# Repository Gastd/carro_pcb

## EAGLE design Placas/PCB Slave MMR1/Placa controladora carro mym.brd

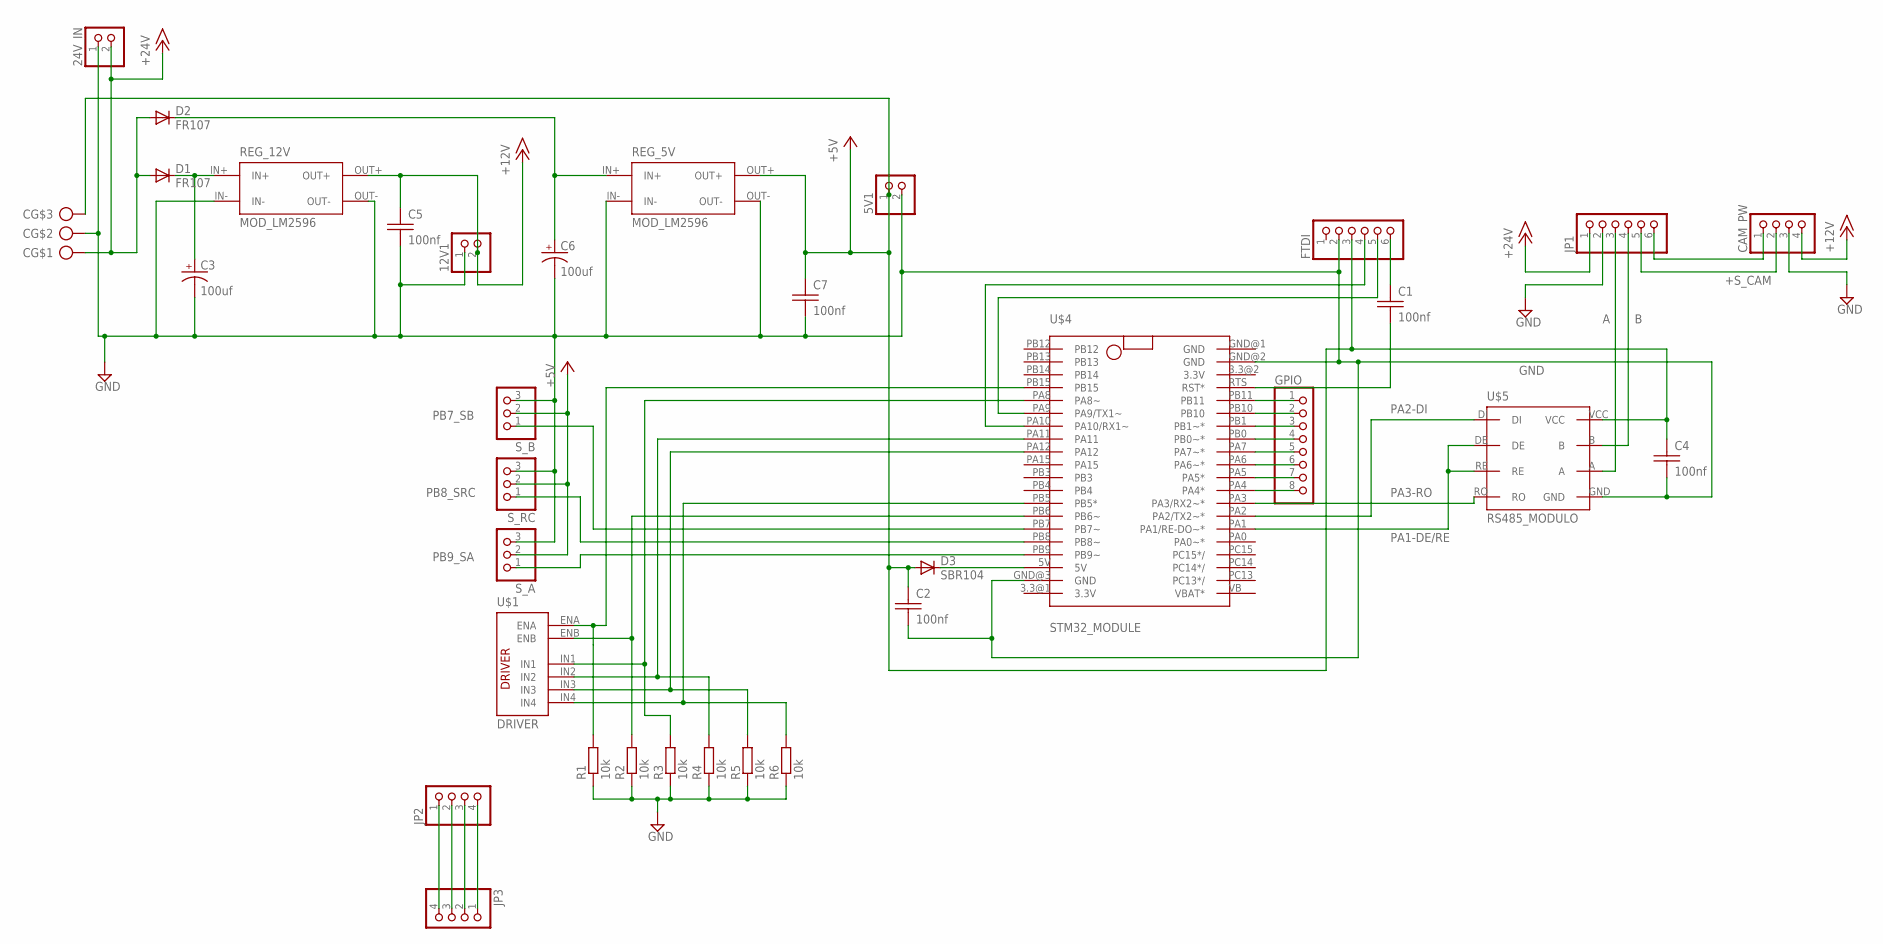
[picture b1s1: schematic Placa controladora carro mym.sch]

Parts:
5V1, 12V1, 24V_IN: PINHD-1X2; 1X02
C: drv; PTR_AK300/3
C1, C2, C4, C5, C7: 100nf; CAP_CER_2,54-5X5
C3, C6: 100uf; CAP_T_5-D8,5
CAM_PW: PINHD-1X4; 1X04
D1, D2: FR107; D-2.5
D3: SBR104; D_SMD
FTDI: PINHD-1X6; 1X06
GPIO: PINHD-1X8; 1X08
JP1: PINHD-1X6; 1X06
JP2, JP3: PINHD-1X4; 1X04
R1, R2, R3, R4, R5, R6: 10k; 0204/7
REG_5V, REG_12V: MOD_LM2596; MOD_LM2596_FP
S_A: PINHD-1X3; 1X03
S_B: PINHD-1X3; 1X03
S_RC: PINHD-1X3; 1X03
U$1: DRIVER
U$4: STM32_MODULE; STM32FP
U$5: RS485_MODULO; RS485_FP

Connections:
+5V: 5V1.1, C.3, C2.1, C4.1, C7.1, D3.A, FTDI.3, REG_5V.OUT+, S_A.2, S_B.2, S_RC.2, U$5.VCC
+12V: 12V1.2, C5.1, REG_12V.OUT+
+15V: 24V_IN.2, C.1, CAM_PW.4, D1.A, D2.A, JP1.1
+S_CAM: CAM_PW.2, JP1.5
A: JP1.3, U$5.A
B: JP1.4, U$5.B
ENA: R1.2, U$1.ENA, U$4.PB15
ENEB: R2.2, U$1.ENB, U$4.PB6 (PB6~)
GND: 5V1.2, 12V1.1, 24V_IN.1, C.2, C2.2, C3.-, C4.2, C5.2, C6.-, C7.2, CAM_PW.3, FTDI.2, JP1.2, R1.1, R2.1, R3.1, R4.1, R5.1, R6.1, REG_5V.IN-, REG_5V.OUT-, REG_12V.IN-, REG_12V.OUT-, S_A.3, S_B.3, S_RC.3, U$4.GND@2 (GND), U$4.GND@3 (GND), U$5.GND
IN1: R3.2, U$1.IN1, U$4.PA8 (PA8~)
IN2: R4.2, U$1.IN2, U$4.PA11
IN3: R5.2, U$1.IN3, U$4.PA12
IN4: R6.2, U$1.IN4, U$4.PB5 (PB5*)
unnamed: D3.K (C), U$4.5V
unnamed: C6.+, D2.C, REG_5V.IN+
unnamed: C3.+, D1.C, REG_12V.IN+
unnamed: CAM_PW.1, JP1.6
unnamed: JP2.1, JP3.4
unnamed: FTDI.4, U$4.PA10 (PA10/RX1~)
unnamed: FTDI.5, U$4.PA9 (PA9/TX1~)
unnamed: C1.1, FTDI.6
unnamed: C1.2, U$4.RTS (RST*)
unnamed: JP2.2, JP3.3
unnamed: JP2.3, JP3.2
unnamed: JP2.4, JP3.1
unnamed: GPIO.1, U$4.PB11
unnamed: GPIO.2, U$4.PB10
unnamed: GPIO.3, U$4.PB1 (PB1~*)
unnamed: GPIO.4, U$4.PB0 (PB0~*)
unnamed: GPIO.5, U$4.PA7 (PA7~*)
unnamed: GPIO.6, U$4.PA6 (PA6~*)
unnamed: GPIO.7, U$4.PA5 (PA5*)
unnamed: GPIO.8, U$4.PA4 (PA4*)
PA1-DE/RE: U$4.PA1 (PA1/RE-DO~*), U$5.DE, U$5.RE
PA2-DI: U$4.PA2 (PA2/TX2~*), U$5.DI
PA3-RO: U$4.PA3 (PA3/RX2~*), U$5.RO
PB7_SB: S_B.1, U$4.PB7 (PB7~)
PB8_SRC: S_RC.1, U$4.PB8 (PB8~)
PB9_SA: S_A.1, U$4.PB9 (PB9~)

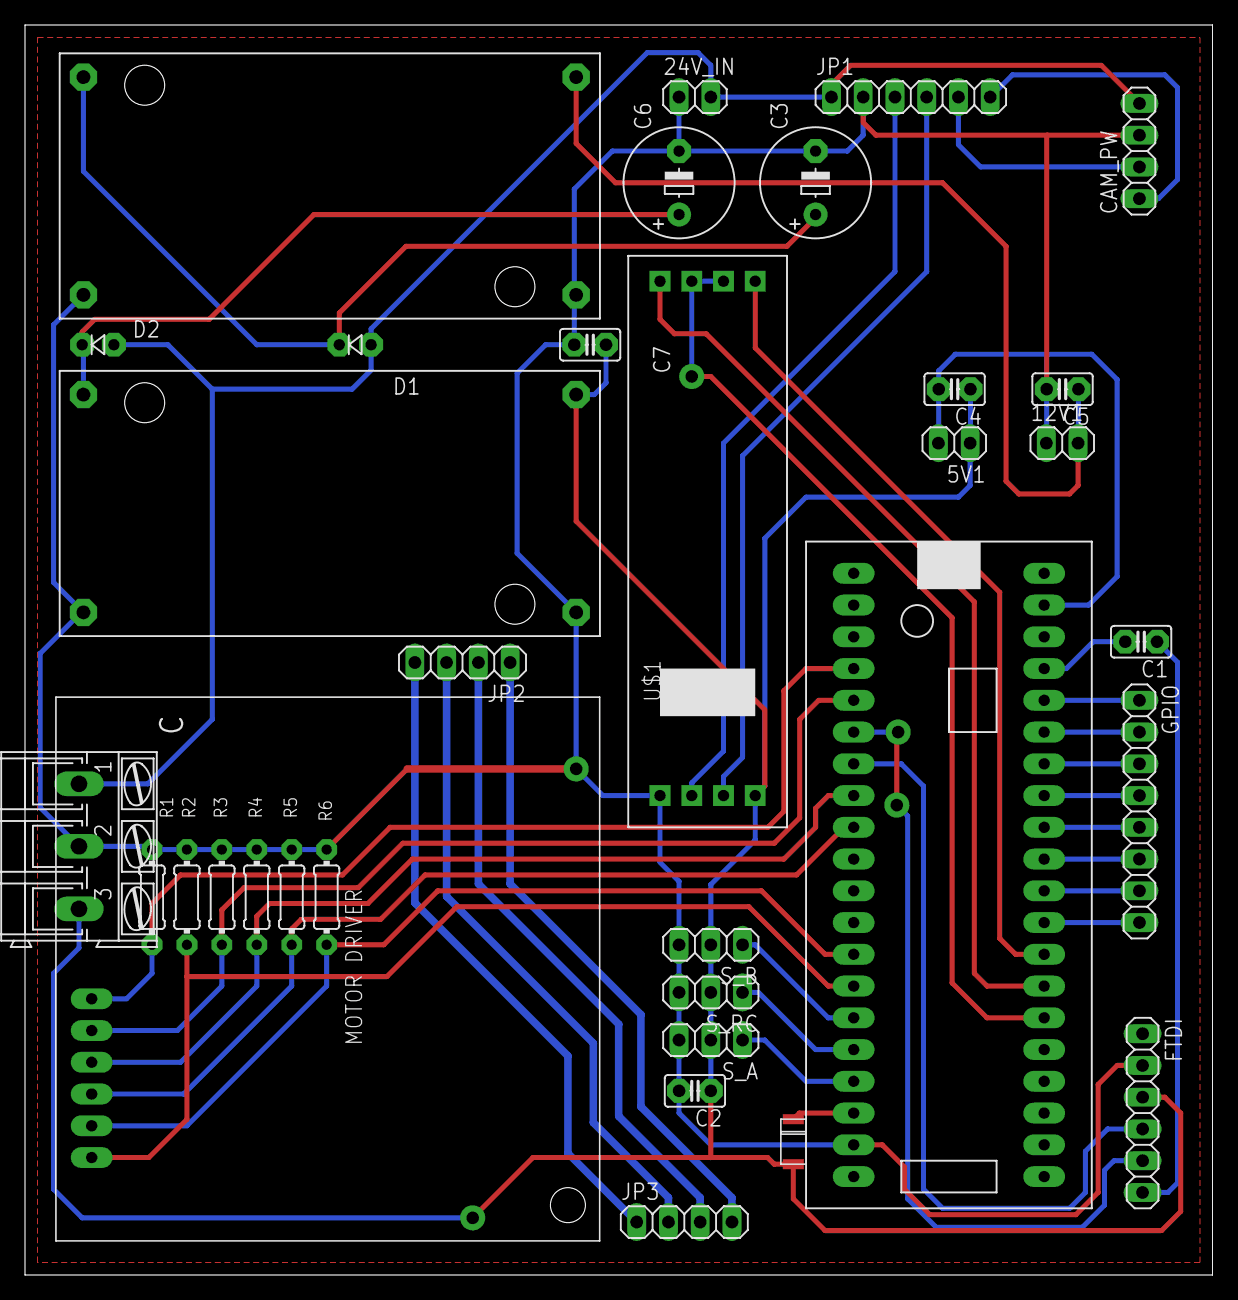
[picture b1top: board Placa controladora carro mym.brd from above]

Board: 2 copper layers, 95.0 x 100.0 mm, 34 parts (0 on the bottom side), 39 nets.

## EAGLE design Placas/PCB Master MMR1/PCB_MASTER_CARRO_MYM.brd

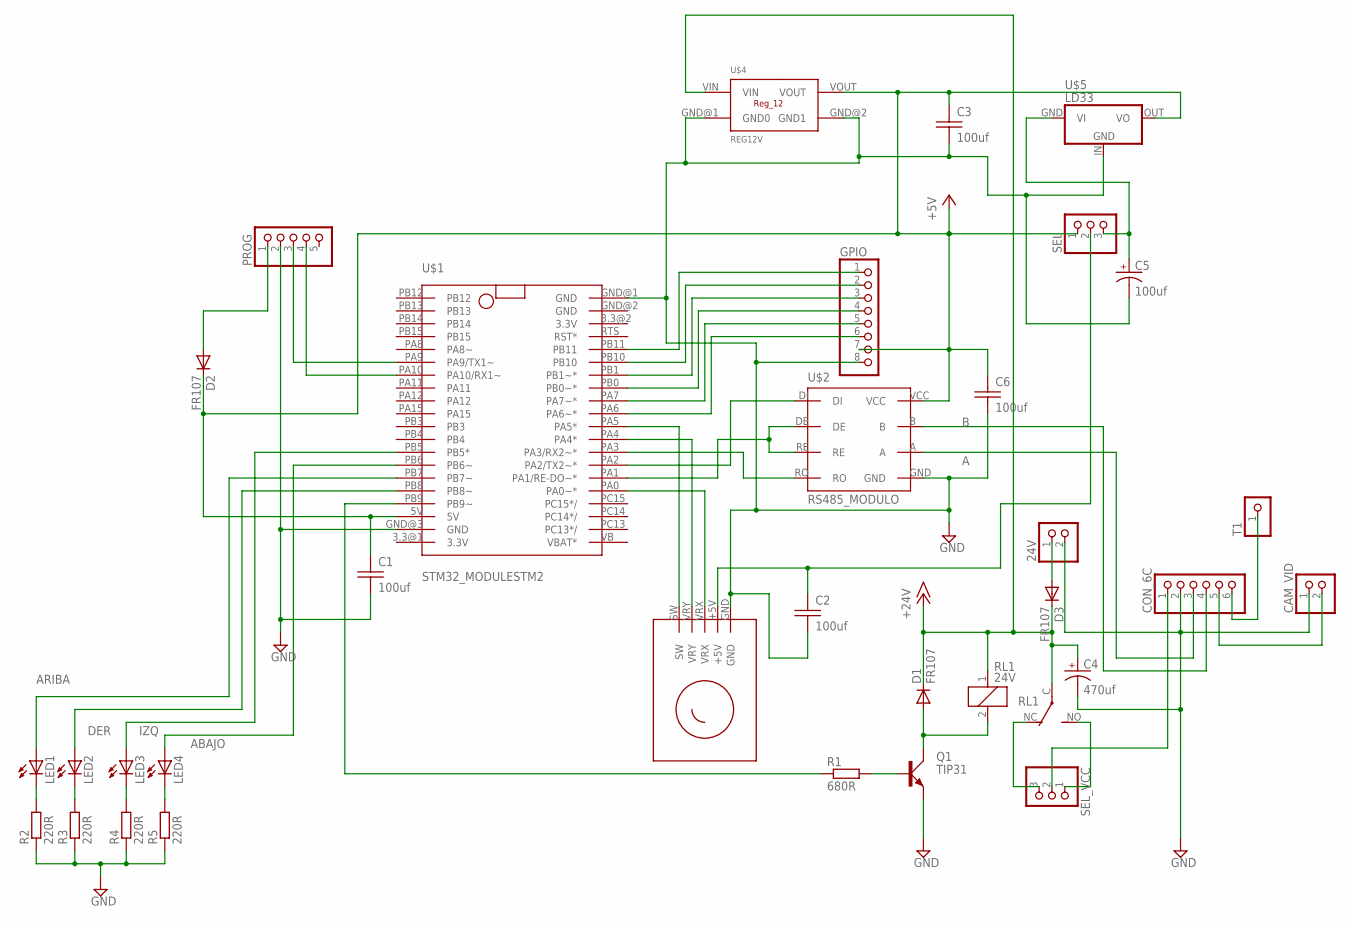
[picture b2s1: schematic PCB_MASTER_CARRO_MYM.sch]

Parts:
24V: PINHD-1X2; 1X02
C1, C2, C3, C6: 100uf; CAP_CER_2,54-5X5
C4: 470uf; CAP_T_5-D8,5
C5: 100uf; CAP_T_3,5-D8
CAM_VID: PINHD-1X2; 1X02
CON_6C: PINHD-1X6; 1X06
D1: FR107; D-5
D2, D3: FR107; DIODO4MM
GPIO: PINHD-1X8; 1X08
LED1, LED2, LED3, LED4: LEDLED_T_3MM; LED3MM
PROG: PINHD-1X5; 1X05
Q1: TIP31; TO220
R1: 680R; 0204/5
R2, R3, R4, R5: 220R; 0204/5
RL1: 24V; CQ1
SEL: PINHD-1X3; 1X03
SEL_VCC: PINHD-1X3; 1X03
T1: PINHD-1X1; 1X01
U$1: STM32_MODULESTM2; STM_32MOD
U$2: RS485_MODULO; RS485_FP
U$3: JOYSTICK
U$4: REG12V
U$5: LD33; 78XXS

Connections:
+5V: C1.1, C3.1, C6.1, D2.C, GPIO.7, SEL.1, U$1.5V, U$2.VCC, U$4.VOUT, U$5.OUT (VO)
+15V: C4.+, D1.C, D3.C, RL1.1, RL1.C, U$4.VIN
A: CON_6C.3, U$2.A
ABAJO: LED4.A, U$1.PB6 (PB6~)
ARIBA: LED1.A, U$1.PB7 (PB7~)
B: CON_6C.4, U$2.B
DER: LED2.A, U$1.PB8 (PB8~)
GND: 24V.2, C1.2, C2.2, C3.2, C4.-, C5.-, C6.2, CAM_VID.1, CON_6C.2, GPIO.8, PROG.2, Q1.E, R2.1, R3.1, R4.1, R5.1, U$1.GND@1 (GND), U$1.GND@3 (GND), U$2.GND, U$3.GND, U$4.GND@1 (GND0), U$4.GND@2 (GND1), U$5.IN (GND)
IZQ: LED3.A, U$1.PB5 (PB5*)
unnamed: C5.+, SEL.3, U$5.GND (VI)
unnamed: LED1.K (C), R2.2
unnamed: LED2.K (C), R3.2
unnamed: LED3.K (C), R4.2
unnamed: LED4.K (C), R5.2
unnamed: 24V.1, D3.A
unnamed: U$1.PA1 (PA1/RE-DO~*), U$2.DE, U$2.RE
unnamed: U$1.PA2 (PA2/TX2~*), U$2.DI
unnamed: U$1.PA3 (PA3/RX2~*), U$2.RO
unnamed: D1.A, Q1.C, RL1.2
unnamed: C2.1, SEL.2, U$3.+5V
unnamed: Q1.B, R1.2
unnamed: R1.1, U$1.PB9 (PB9~)
unnamed: RL1.NC (O), SEL_VCC.3
unnamed: CAM_VID.2, CON_6C.5
unnamed: RL1.NO (S), SEL_VCC.1
unnamed: CON_6C.1, SEL_VCC.2
unnamed: GPIO.6, U$1.PA6 (PA6~*)
unnamed: GPIO.5, U$1.PA7 (PA7~*)
unnamed: GPIO.4, U$1.PB0 (PB0~*)
unnamed: GPIO.3, U$1.PB1 (PB1~*)
unnamed: GPIO.2, U$1.PB10
unnamed: GPIO.1, U$1.PB11
unnamed: D2.A, PROG.1
unnamed: CON_6C.6, T1.1
RX-TX_A9: PROG.3, U$1.PA9 (PA9/TX1~)
SW: U$1.PA0 (PA0~*), U$3.VRX
TX-RX_A10: PROG.4, U$1.PA10 (PA10/RX1~)
VRX: U$1.PA5 (PA5*), U$3.SW
VRY: U$1.PA4 (PA4*), U$3.VRY

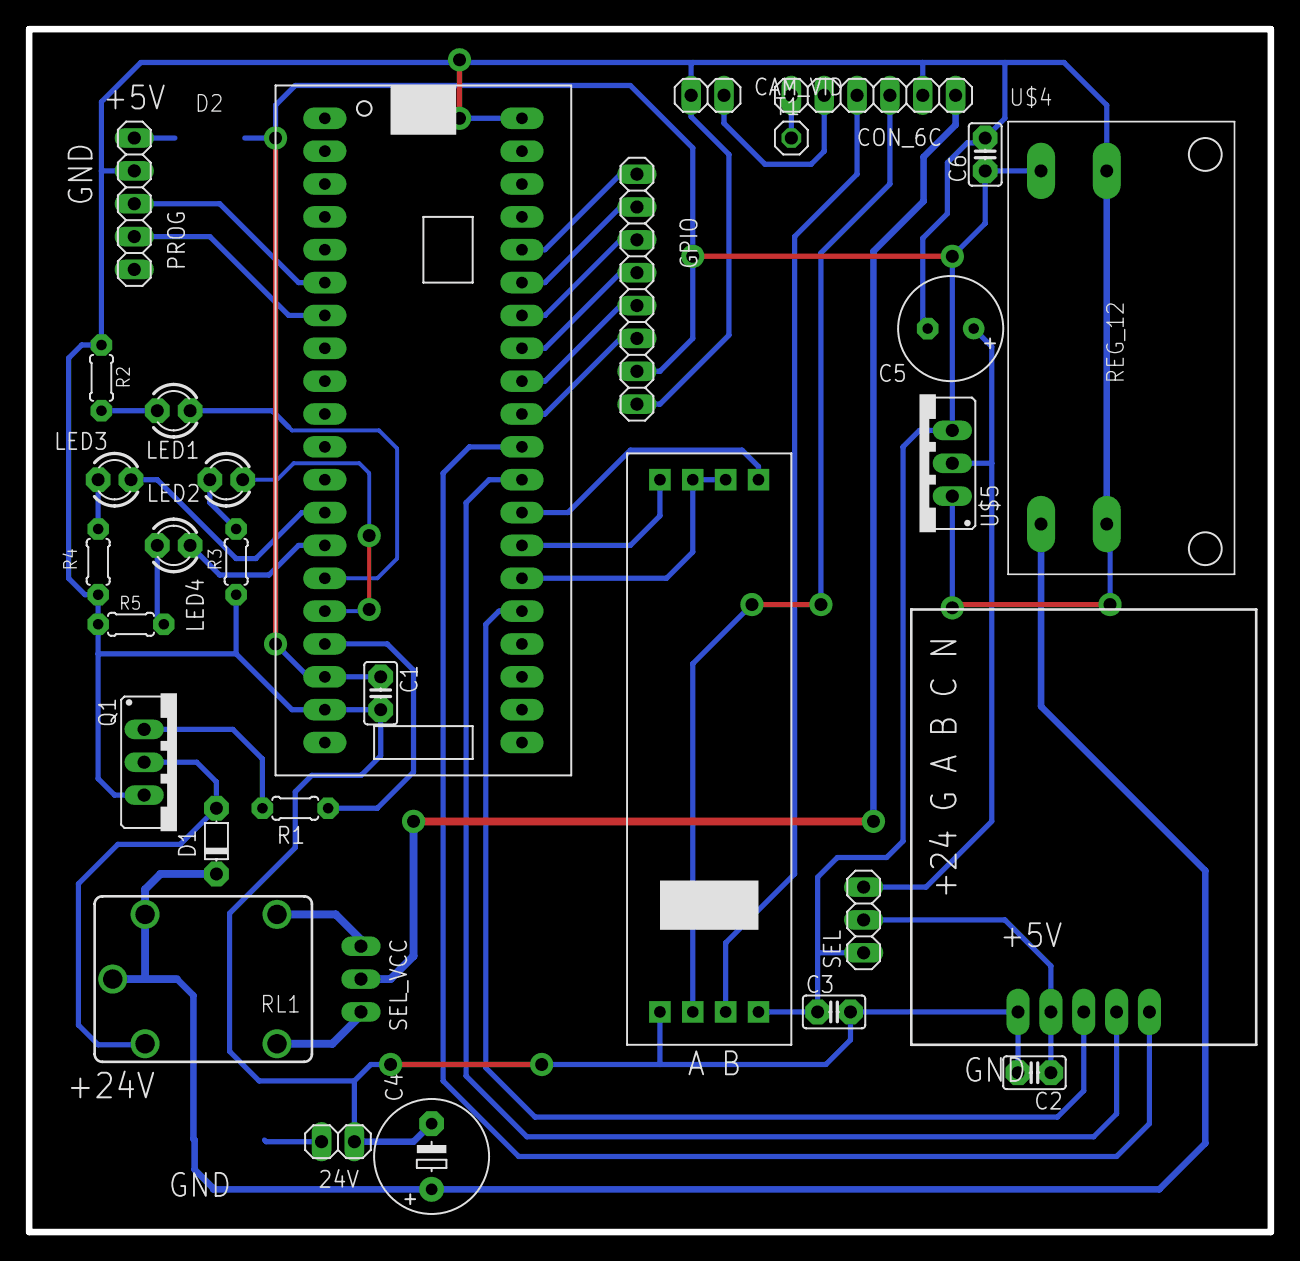
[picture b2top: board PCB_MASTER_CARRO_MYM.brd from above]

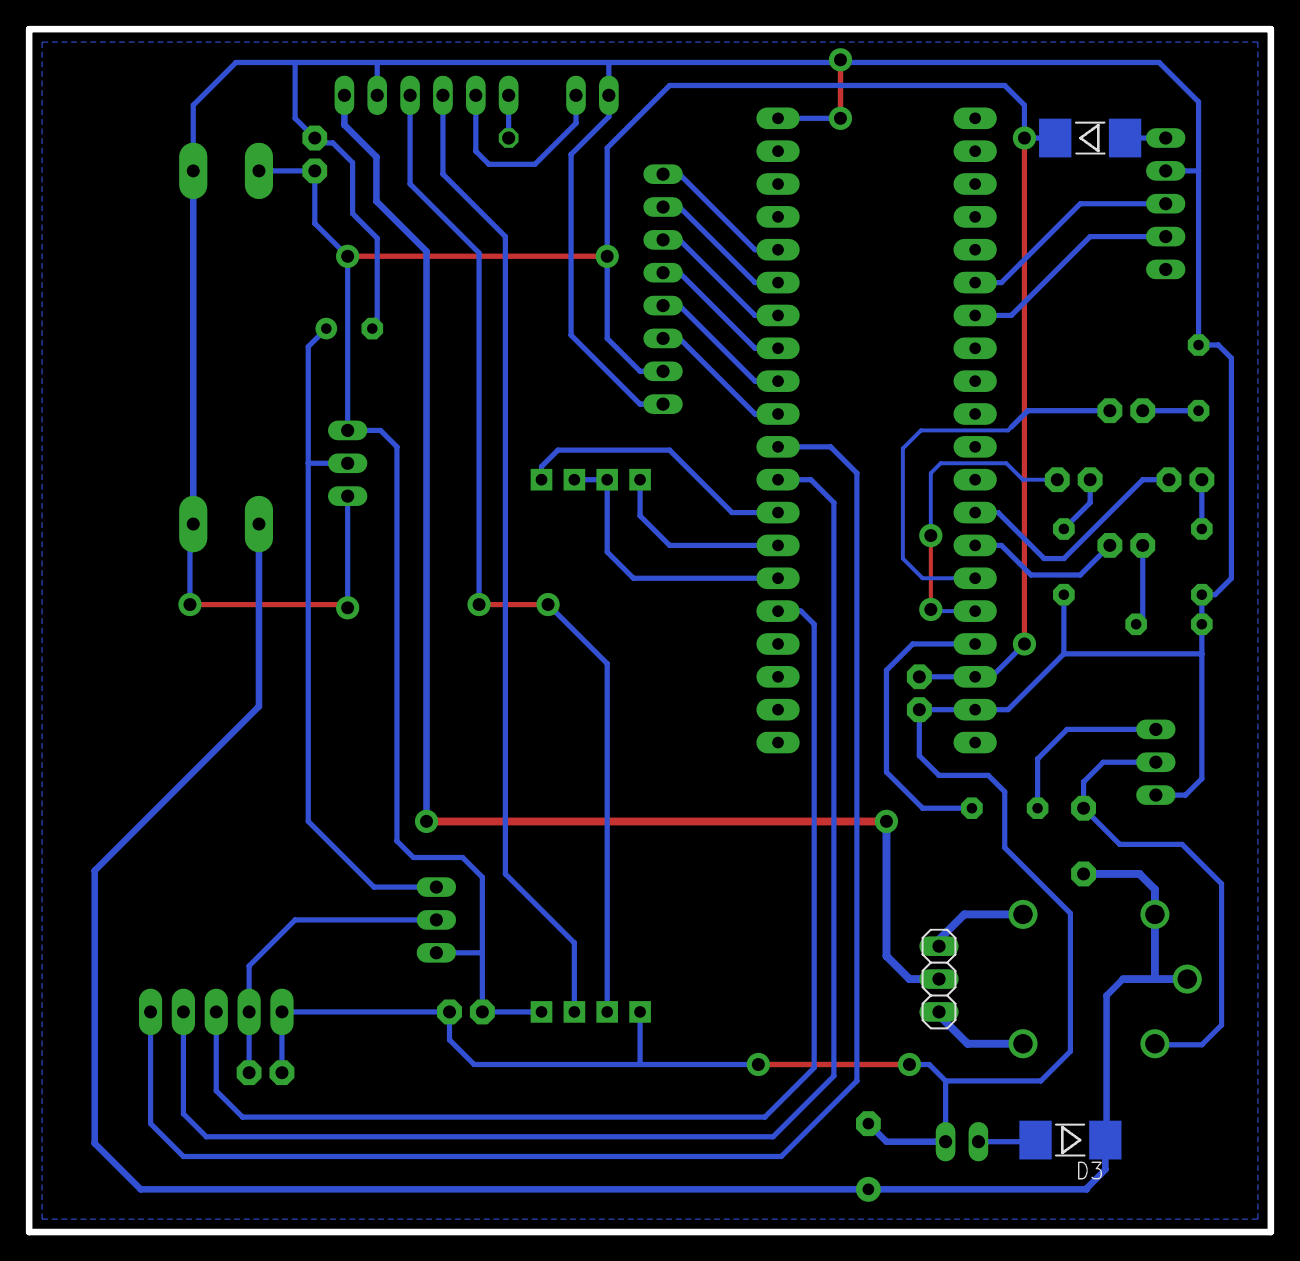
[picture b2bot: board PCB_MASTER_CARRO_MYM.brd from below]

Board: 2 copper layers, 96.0 x 93.0 mm, 33 parts (3 on the bottom side), 39 nets.

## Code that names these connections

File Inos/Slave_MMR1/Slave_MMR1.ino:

#include <Servo.h>

#define led PC13      // Para hacer blink y testar codigos
#define cs '>'        // Caracter separador mensaje
#define re_de PA1     // Pin de activscion RS485 

//***************** Controle carro ***************//
///-----
#define ENA PA8         // ENABLE MOTOR IZQ
#define ENB PB6        // ENABLE MOTOR DER

///----- MOTOR der
#define IN1 PB15
#define IN2 PB10
///----- MOTOR izq
#define IN3 PB11
#define IN4 PB5

//************ Controle camera *********************//
#define sb PB7            // SERVO BASE
#define src PB8           // SERVO ROTACION CAMARA
//#define sa PB9            // SERVO AUXILIAR "SENSOR DE PROXIMIDADE"

// pwm zero servos
#define zero_sb 98   // zero servo base -- 10 -120
#define zero_src 84  // zero servo -- rango de valores 25-180
//SB --- min25 - max180 
#define min_sb 25   
#define max_sb 180
//SRC ---- min10 - max120
#define min_src 10
#define max_src 120


// Variables temporales
int pwm_c = 0;
int tempo = 0;
int con = 0;

bool value_led = true;

//********* Inicilizar objetos tipo servo *********//
Servo s_base;
Servo s_rot_camera;
//Servo s_aux;


void setup() {
  //*************- Inicializa comunicacion ********************/
  // porta serial para comunicacion rs485
  Serial1.begin(115200);
  Serial1.setTimeout(100);
  //Serial.begin(115200);
  //Serial.setTimeout(100);

  //******** Servos asignacion de pines *************/
  s_base.attach(sb); // base 
  s_rot_camera.attach(src); //rota camera
  //s_aux.attach(sa); // auxiliar

  s_base.write(zero_sb);
  s_rot_camera.write(zero_src);
  //s_aux.write(0);

  // For blink led or anything else
  pinMode(led, OUTPUT);
  digitalWrite(led, 0);

  // for RS485 activation
  pinMode(re_de, OUTPUT);
  digitalWrite(re_de, 0);

  pinMode(ENA, OUTPUT);
  pinMode(ENB, OUTPUT);
  pinMode(IN1, OUTPUT);
  pinMode(IN2, OUTPUT);
  pinMode(IN3, OUTPUT);
  pinMode(IN4, OUTPUT);

  digitalWrite(ENA, 0);
  digitalWrite(ENB, 0);
  digitalWrite(IN1, 0);
  digitalWrite(IN2, 0);
  digitalWrite(IN3, 0);
  digitalWrite(IN4, 0);

  // Start blink
  blink_led(500);

  // Envio un 9 para decir que la comunicacion está funcionando
  serial_print_cs(String(9), 1);

  delay(100);

}

void loop() {
  read_input_data();
  delay(10);
}

/***** Funcion de lectura de parametros *****/
void read_input_data(){
  if(Serial1.available() != 0){
    String data_in = Serial1.readStringUntil(cs);
    int sel_action = data_in.toInt();
    data_in = Serial1.readStringUntil(cs);
    int direction_m = data_in.toInt();
    data_in = Serial1.readStringUntil(cs);
    int pwm_mov = data_in.toInt();
    data_in = Serial1.readStringUntil(cs);
    int tempo_mov = data_in.toInt();

    switch (sel_action){
      case 1:
        mover_carro(direction_m, pwm_mov, tempo_mov);
        break;
      case 2:
        // angulo *** Diferentes limites
        mover_camera(direction_m, pwm_mov, tempo_mov); 
        //blink_led(80);
        break;
      case 3: // responde
        blink_led(300);
        mover_sensor(pwm_mov, tempo_mov);
        break;
      case 4: // responde para inicio de los comando
        blink_led(tempo_mov);
        serial_print_cs("500", 0);
        //delay(2000);
        blink_led(tempo_mov);
        String msn_c = String(con);
        serial_print_cs(msn_c, 0);
        con += 10;
        break;
      }// End Switch
   }// End Serial1 available 
}// End function read input data serial


/*************************************************************************/
/***************** Mover carro -- funciones -- ***************************/
void mover_carro(int dir, int pwm_m, int time_m){
  switch (dir) {
    case 0:
        para_tudo(0);
        break;
    case 1:
        frente(pwm_m, time_m);
        break;
    case 2:
        atras(pwm_m, time_m);
        break;
    case 3:
        esquerda(pwm_m, time_m);
        break;
    case 4:
        direita(pwm_m, time_m);
        break;
    }// End Switch
}

void frente(int pwm_c, int tempo) {
  pwm_control(pwm_c);
  digitalWrite(IN1, 1);
  digitalWrite(IN2, 0);
  digitalWrite(IN3, 1);
  digitalWrite(IN4, 0);
  blink_led(int(tempo/3));
  para_tudo(0);
  serial_print_cs("O", 0);
  serial_print_cs("Movendo para frente", 0);
}

void atras(int pwm_c, int tempo) {
  pwm_control(pwm_c);
  digitalWrite(IN1, 0);
  digitalWrite(IN2, 1);
  digitalWrite(IN3, 0);
  digitalWrite(IN4, 1);
  blink_led(int(tempo/3));
  para_tudo(0);
  serial_print_cs("O", 0);
  serial_print_cs("Movendo para atras", 0);
}

void esquerda(int pwm_c, int tempo) {
  pwm_control(pwm_c);
  digitalWrite(IN1, LOW);
  digitalWrite(IN2, HIGH);
  digitalWrite(IN3, HIGH);
  digitalWrite(IN4, LOW);
  blink_led(int(tempo/3));
  para_tudo(0);
  serial_print_cs("O", 0);
  serial_print_cs("Movendo para esquerda", 0);
}

void direita(int pwm_c, int tempo) {
  pwm_control(pwm_c);
  digitalWrite(IN1, HIGH);
  digitalWrite(IN2, LOW);
  digitalWrite(IN3, LOW);
  digitalWrite(IN4, HIGH);
  blink_led(tempo/3);
  para_tudo(0);
  serial_print_cs("O", 0);
  serial_print_cs("Movendo para direita", 0);
}

void para_tudo(int pwm_c) {
  for(int i=255; i>0; i-10){
    pwm_control(i);
    delay(5);
  }
  digitalWrite(IN1, LOW);
  digitalWrite(IN2, LOW);
  digitalWrite(IN3, LOW);
  digitalWrite(IN4, LOW);
}

void pwm_control(int pwm) {
  analogWrite(ENA, pwm);
  analogWrite(ENB, pwm);
}

/************* Mover camara ******************/
void mover_camera(int sel_motor, int ang_sb, int ang_src){
  if(ang_sb >= min_sb && ang_sb <= max_sb){ //min10 -max120
    s_base.write(ang_sb);
  }
  if(ang_src >= min_src && ang_src <= max_src){ //min25- max180
    s_rot_camera.write(ang_src);
  }
}

/************* Mover sensor de proximidade *****************/
void mover_sensor(int time_sm, int pwm_sm){
    digitalWrite(led, !value_led);
    delay(time_sm);
}

/*********** Comunicacion mensaje de respuesta *************/
void serial_print_cs(String str_out, boolean ini_s){
  if(ini_s){
    for(int i=0; i<5; i++){
      digitalWrite(re_de, 1);
      str_out = str_out + cs;
      Serial1.print(str_out);
      Serial1.flush();
      delay(10);
      digitalWrite(re_de, 0);
      delay(500);
    }
  }else{
    digitalWrite(re_de, 1);
    str_out = str_out + cs;
    Serial1.print(str_out);
    Serial1.flush();
    delay(10);
    digitalWrite(re_de, 0);
  }
}

/************** Blink led PC13 *******************/
void blink_led(int time_b){
  digitalWrite(led, 0);
  delay(time_b);
  digitalWrite(led, 1);
  delay(time_b);
  digitalWrite(led, 0);
  delay(time_b);
  digitalWrite(led, 1);
}

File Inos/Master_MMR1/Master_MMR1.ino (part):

#define led PC13
#define cs '>'
#define re_de PA1
#define relay_slave_ctrl PB9

// leds para visualizar
#define arriba PB7
#define der PB8
#define izq PB5
#define abajo PB6

#define SW_joystick PA5
#define joystick_X PA0
#define joystick_Y PA4

int c_s = 0;
bool switch_cont = true;
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
  // configuracion de los pinos
  pinMode(arriba, OUTPUT);
  pinMode(der, OUTPUT);
  pinMode(izq, OUTPUT);
  pinMode(abajo, OUTPUT);
  all_off(0);

  pinMode(relay_slave_ctrl, OUTPUT);
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
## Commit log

2018-09-08 Add library arduino nano
2018-09-08 Update library
2018-09-08 Add arduino code
2019-01-18 Colocando todo junto
    plascas y codigo en arduino
2019-01-18 Version 1 funcionando
    placas e inos, falta colocar isolamento de USB
2019-01-18 joystick funcionando
    adicionado el control por joystick
